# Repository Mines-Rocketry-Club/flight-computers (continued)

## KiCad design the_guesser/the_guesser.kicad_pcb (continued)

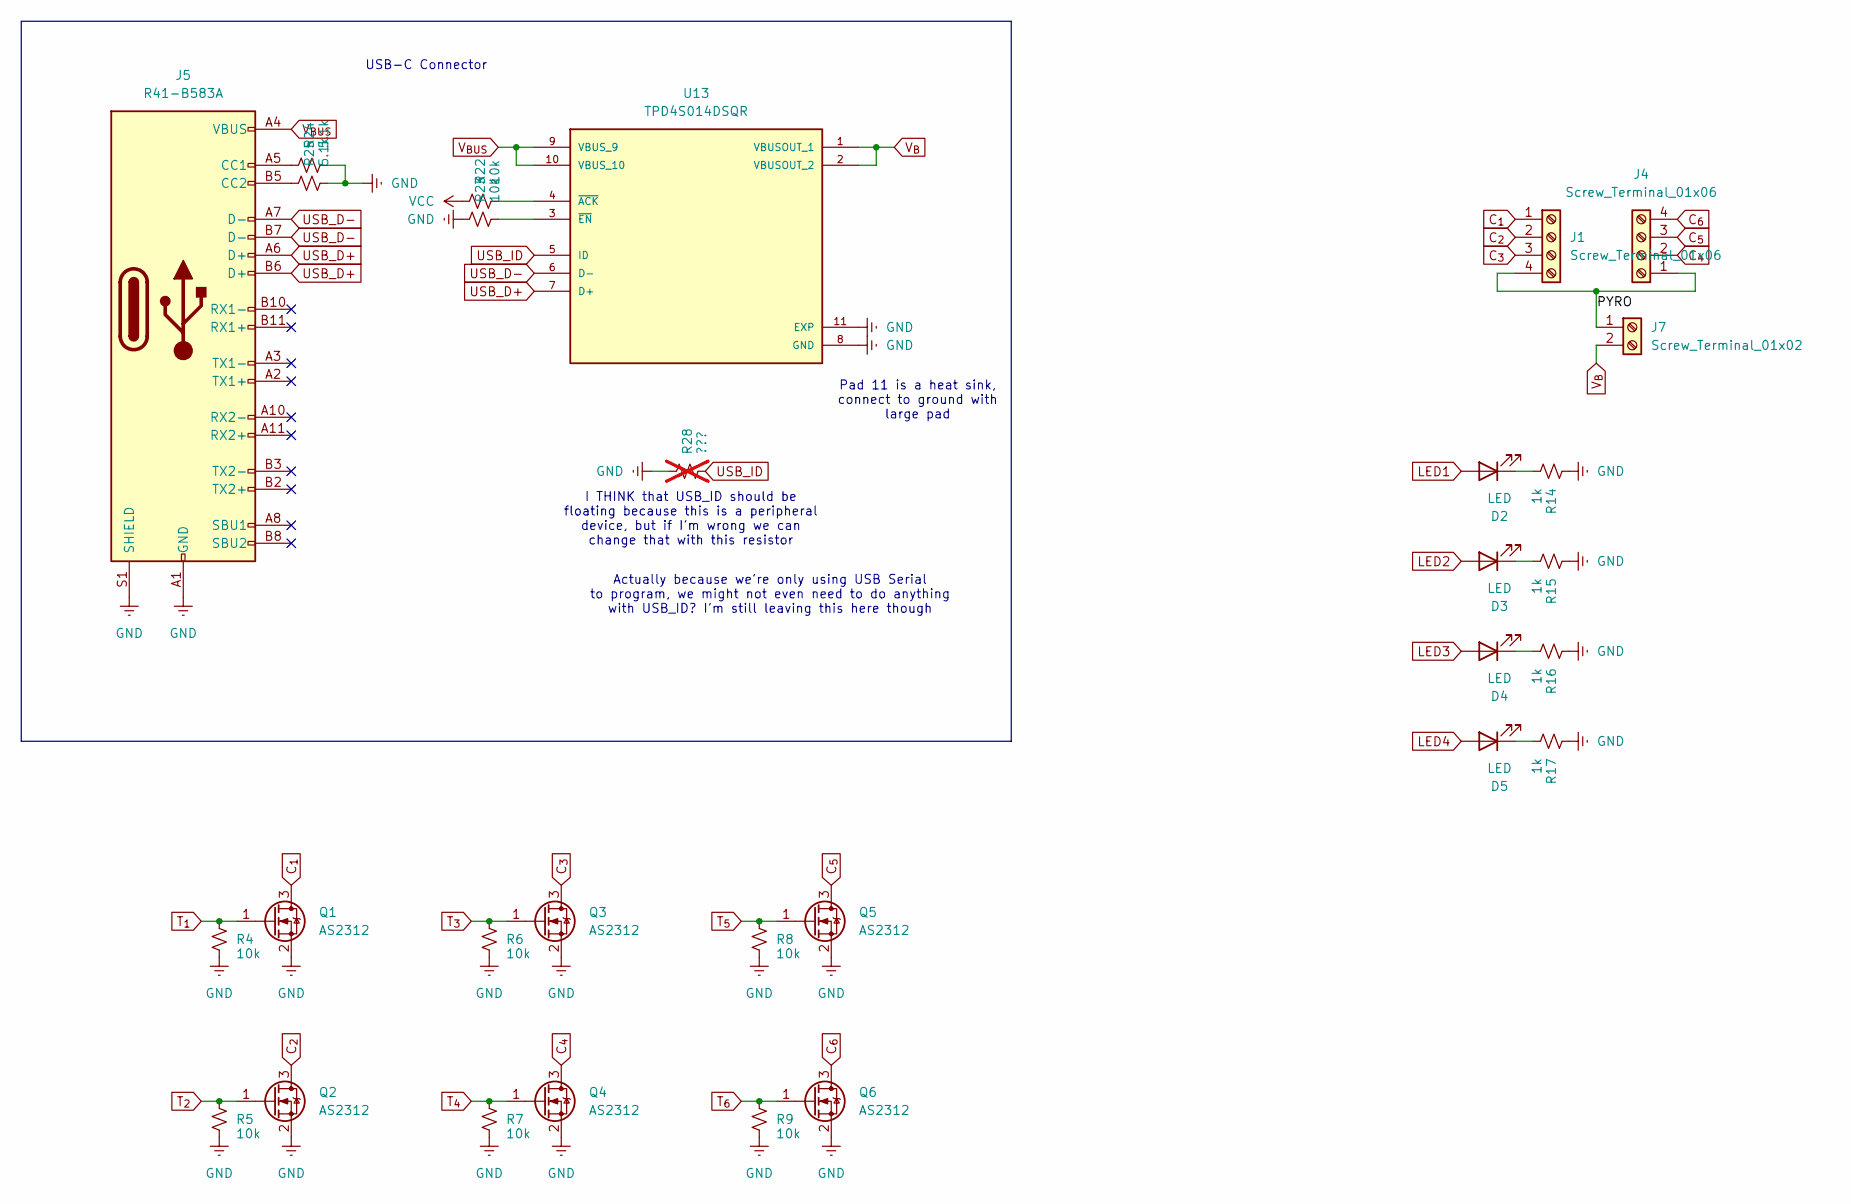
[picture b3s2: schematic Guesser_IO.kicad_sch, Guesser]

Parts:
D2, D3, D4, D5: LED; LED_0603_1608Metric
J1, J4: Screw_Terminal_01x06; TerminalBlock_Phoenix_MPT-0,5-4-2.54_1x04_P2.54mm_Horizontal
J5: R41-B583A; CONN_R41-B583A_MIT
J7: Screw_Terminal_01x02; TerminalBlock_Phoenix_MPT-0,5-2-2.54_1x02_P2.54mm_Horizontal
Q1, Q2, Q3, Q4, Q5, Q6: AS2312; SOT-23
R4, R5, R6, R7, R8, R9, R22, R23: 10k; R_0603_1608Metric
R14, R15, R16, R17: 1k; R_0603_1608Metric
R24, R25: 5.1k; R_0603_1608Metric
R28: ???; R_0603_1608Metric; not fitted
U13: TPD4S014DSQR; PARTREV E

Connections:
/Inputs Outputs/PYRO: J1.4, J4.1, J7.1
C_{1}: J1.1, Q1.3 (D)
C_{2}: J1.2, Q2.3 (D)
C_{3}: J1.3, Q3.3 (D)
C_{4}: J4.2, Q4.3 (D)
C_{5}: J4.3, Q5.3 (D)
C_{6}: J4.4, Q6.3 (D)
GND: J5.A1 (GND), J5.A12 (GND), J5.B1 (GND), J5.B12 (GND), J5.S1 (SHIELD), Q1.2 (S), Q2.2 (S), Q3.2 (S), Q4.2 (S), Q5.2 (S), Q6.2 (S), R4.2, R5.2, R6.2, R7.2, R8.2, R9.2, R14.1, R15.1, R16.1, R17.1, R23.1, R24.2, R25.2, R28.1, U13.8 (GND), U13.11 (EXP); also elsewhere on the board
LED1: D2.2 (A); also elsewhere on the board
LED2: D3.2 (A); also elsewhere on the board
LED3: D4.2 (A); also elsewhere on the board
LED4: D5.2 (A); also elsewhere on the board
unnamed: D2.1 (K), R14.2
unnamed: D3.1 (K), R15.2
unnamed: D4.1 (K), R16.2
unnamed: D5.1 (K), R17.2
unnamed: J5.A5 (CC1), R24.1
unnamed: J5.B5 (CC2), R25.1
unnamed: R22.2, U13.4 (~ACK)
unnamed: R23.2, U13.3 (~EN)
T_{1}: Q1.1 (G), R4.1; also elsewhere on the board
T_{2}: Q2.1 (G), R5.1; also elsewhere on the board
T_{3}: Q3.1 (G), R6.1; also elsewhere on the board
T_{4}: Q4.1 (G), R7.1; also elsewhere on the board
T_{5}: Q5.1 (G), R8.1; also elsewhere on the board
T_{6}: Q6.1 (G), R9.1; also elsewhere on the board
USB_D+: J5.A6 (D+), J5.B6 (D+), U13.7 (D+); also elsewhere on the board
USB_D-: J5.A7 (D-), J5.B7 (D-), U13.6 (D-); also elsewhere on the board
USB_ID: R28.2, U13.5 (ID)
VCC: R22.1; also elsewhere on the board
V_{BUS}: J5.A4 (VBUS), J5.A9 (VBUS), J5.B4 (VBUS), J5.B9 (VBUS), U13.9 (VBUS_9), U13.10 (VBUS_10)
V_{B}: J7.2, U13.1 (VBUSOUT_1), U13.2 (VBUSOUT_2); also elsewhere on the board

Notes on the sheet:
I THINK that USB_ID should be floating because this is a peripheral device, but if I'm wrong we can change that with this resistor
USB-C Connector
Actually because we're only using USB Serial to program, we might not even need to do anything with USB_ID? I'm still leaving this here though
Pad 11 is a heat sink, connect to ground with large pad

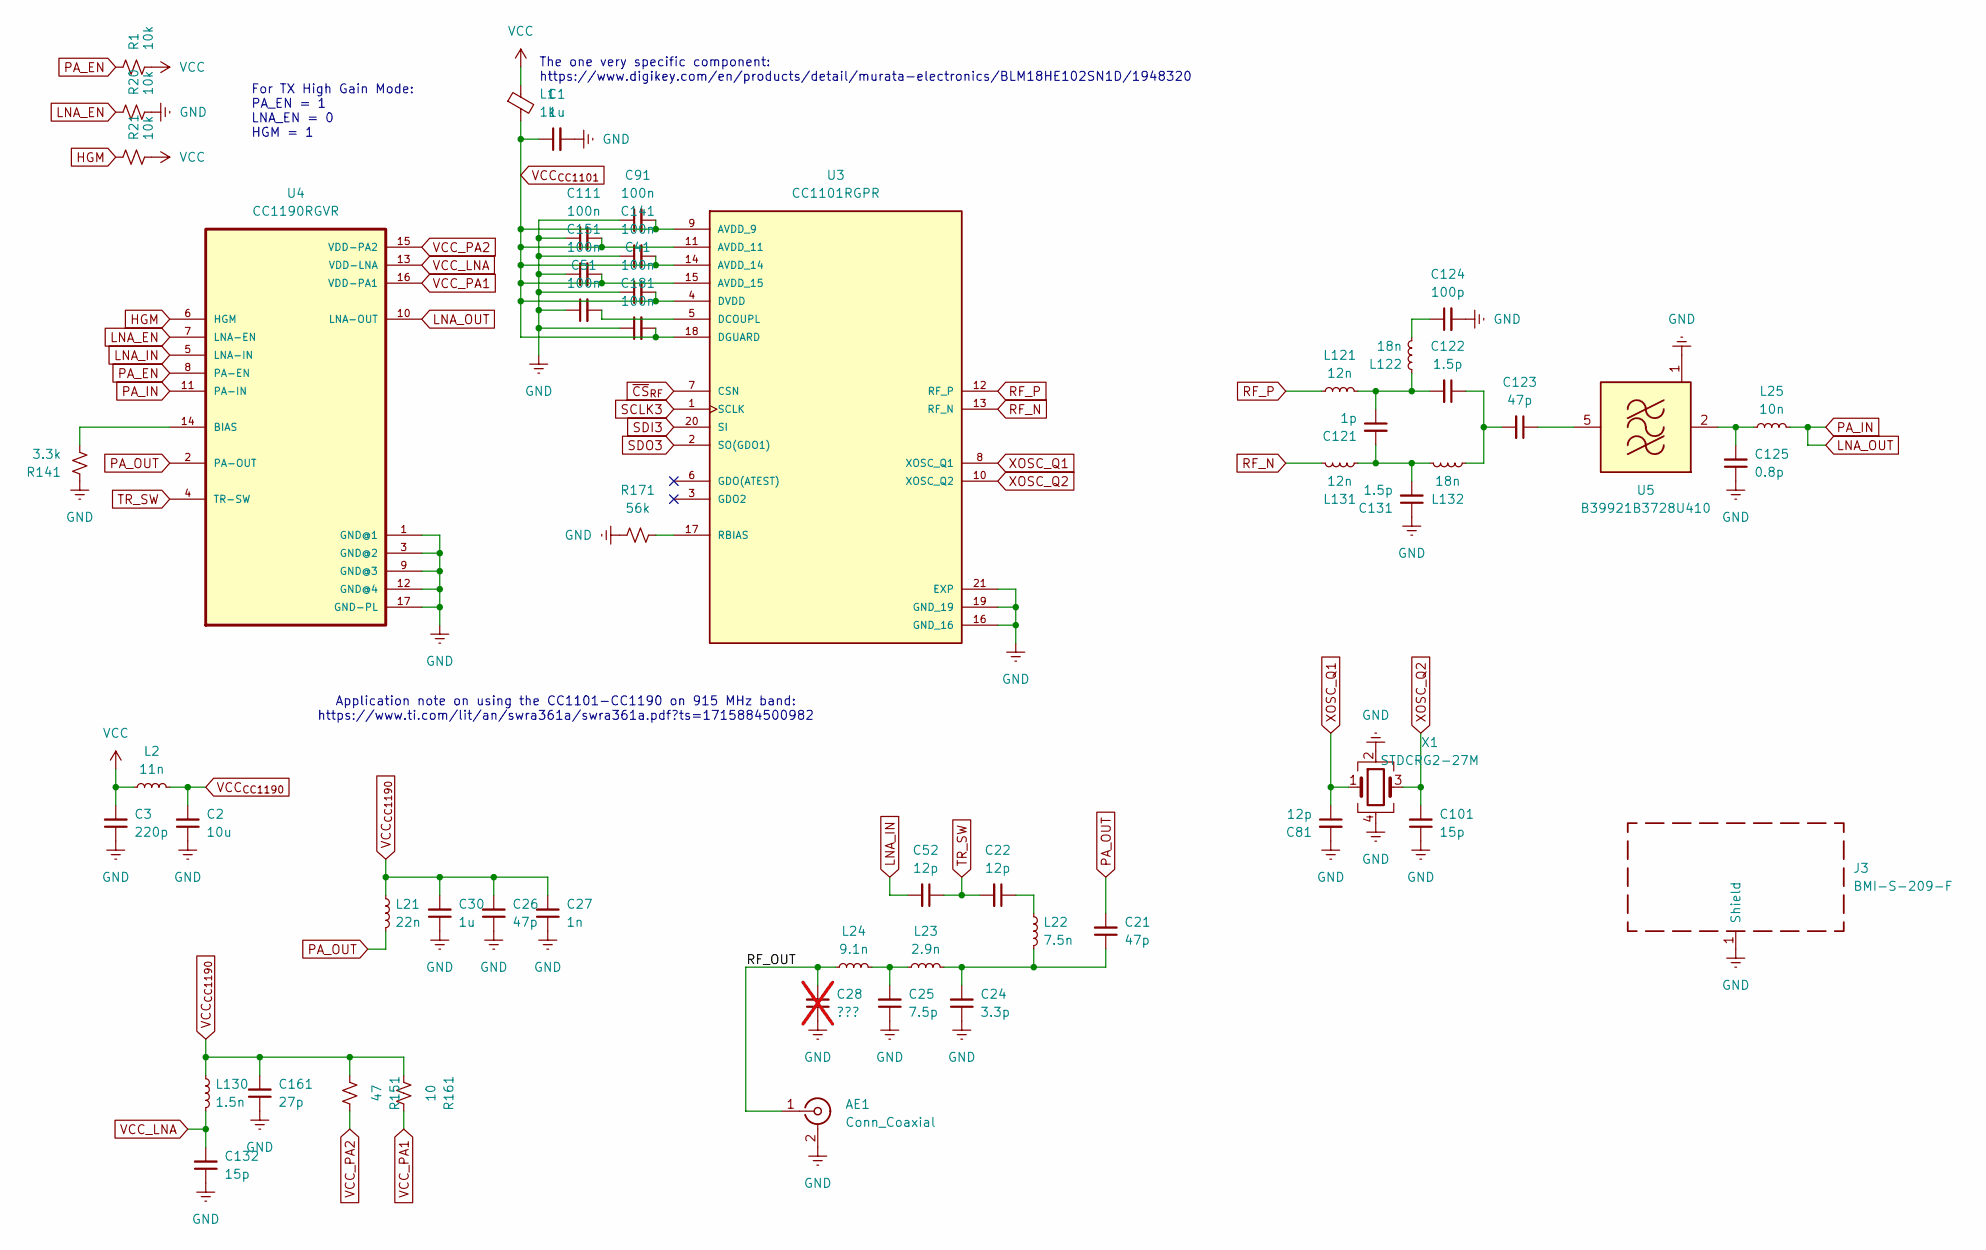
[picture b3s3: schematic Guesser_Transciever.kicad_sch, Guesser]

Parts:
AE1: Conn_Coaxial; SMA_Samtec_SMA-J-P-X-ST-EM1_EdgeMount
C1, C30: 1u; C_0603_1608Metric
C2: 10u; C_0603_1608Metric
C3: 220p; C_0603_1608Metric
C21, C26, C123: 47p; C_0603_1608Metric
C22, C52, C81: 12p; C_0603_1608Metric
C24: 3.3p; C_0603_1608Metric
C25: 7.5p; C_0603_1608Metric
C27: 1n; C_0603_1608Metric
C28: ???; C_0603_1608Metric; not fitted
C41, C51, C91, C111, C141, C151, C181: 100n; C_0603_1608Metric
C101, C132: 15p; C_0603_1608Metric
C121: 1p; C_0603_1608Metric
C122, C131: 1.5p; C_0603_1608Metric
C124: 100p; C_0603_1608Metric
C125: 0.8p; C_0603_1608Metric
C161: 27p; C_0603_1608Metric
J3: BMI-S-209-F; Laird_Technologies_BMI-S-209-F_29.36x18.50mm
L1: 1k; L_0603_1608Metric
L2: 11n; L_0603_1608Metric
L21: 22n; L_0603_1608Metric
L22: 7.5n; L_0603_1608Metric
L23: 2.9n; L_0603_1608Metric
L24: 9.1n; L_0603_1608Metric
L25: 10n; L_0603_1608Metric
L121, L131: 12n; L_0603_1608Metric
L122, L132: 18n; L_0603_1608Metric
L130: 1.5n; L_0603_1608Metric
R1, R20, R21: 10k; R_0603_1608Metric
R141: 3.3k; R_0603_1608Metric
R151: 47; R_0603_1608Metric
R161: 10; R_0603_1608Metric
R171: 56k; R_0603_1608Metric
U3: CC1101RGPR; PARTREV 6-May-2020
U4: CC1190RGVR
U5: B39921B3728U410; Filter_SAW-6_3.8x3.8mm
X1: STDCRG2-27M; Crystal_SMD_3225-4Pin_3.2x2.5mm

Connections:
/Transmitter/RF_OUT: AE1.1 (In), C28.2, L24.1
GND: AE1.2 (Ext), C1.2, C2.1, C3.1, C24.1, C25.1, C26.1, C27.1, C28.1, C30.1, C41.1, C51.1, C81.2, C91.1, C101.1, C111.1, C124.2, C125.1, C131.1, C132.1, C141.1, C151.1, C161.1, C181.1, J3.1 (Shield), R20.2, R141.1, R171.1, U3.16 (GND_16), U3.19 (GND_19), U3.21 (EXP), U4.1 (GND@1), U4.3 (GND@2), U4.9 (GND@3), U4.12 (GND@4), U4.17 (GND-PL), U5.1 (GND), U5.3 (GND), U5.4 (GND), U5.6 (GND), X1.2, X1.4; also elsewhere on the board
HGM: R21.1, U4.6 (HGM)
LNA_EN: R20.1, U4.7 (LNA-EN)
LNA_IN: C52.2, U4.5 (LNA-IN)
LNA_OUT: L25.2, U4.10 (LNA-OUT), U4.11 (PA-IN)
unnamed: C21.1, C24.2, L22.2, L23.2
unnamed: C22.1, L22.1
unnamed: C25.2, L23.1, L24.2
unnamed: C121.1, C122.2, L121.2, L122.1
unnamed: C121.2, C131.2, L131.1, L132.2
unnamed: C122.1, C123.2, L132.1
unnamed: C124.1, L122.2
unnamed: C51.2, U3.5 (DCOUPL)
unnamed: R171.2, U3.17 (RBIAS)
unnamed: R141.2, U4.14 (BIAS)
unnamed: C125.2, L25.1, U5.2 (IN)
unnamed: C123.1, U5.5 (OUT)
PA_EN: R1.1, U4.8 (PA-EN)
PA_OUT: C21.2, L21.2, U4.2 (PA-OUT)
RF_N: L131.2, U3.13 (RF_N)
RF_P: L121.1, U3.12 (RF_P)
SCLK3: U3.1 (SCLK); also elsewhere on the board
SDI3: U3.20 (SI); also elsewhere on the board
SDO3: U3.2 (SO(GDO1)); also elsewhere on the board
TR_SW: C22.2, C52.1, U4.4 (TR-SW)
VCC: C3.2, L1.1, L2.1, R1.2, R21.2; also elsewhere on the board
VCC_LNA: C132.2, L130.2, U4.13 (VDD-LNA)
VCC_PA1: R161.2, U4.16 (VDD-PA1)
VCC_PA2: R151.2, U4.15 (VDD-PA2)
VCC_{CC1101}: C1.1, C41.2, C91.2, C111.2, C141.2, C151.2, C181.2, L1.2, U3.4 (DVDD), U3.9 (AVDD_9), U3.11 (AVDD_11), U3.14 (AVDD_14), U3.15 (AVDD_15), U3.18 (DGUARD)
VCC_{CC1190}: C2.2, C26.2, C27.2, C30.2, C161.2, L2.2, L21.1, L130.1, R151.1, R161.1
XOSC_Q1: C81.1, U3.8 (XOSC_Q1), X1.1
XOSC_Q2: C101.2, U3.10 (XOSC_Q2), X1.3
~CS_{RF}: U3.7 (CSN); also elsewhere on the board

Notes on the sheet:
For TX High Gain Mode: PA_EN = 1 LNA_EN = 0 HGM = 1
Application note on using the CC1101-CC1190 on 915 MHz band: https://www.ti.com/lit/an/swra361a/swra361a.pdf?ts=1715884500982
The one very specific component: https://www.digikey.com/en/products/detail/murata-electronics/BLM18HE102SN1D/1948320

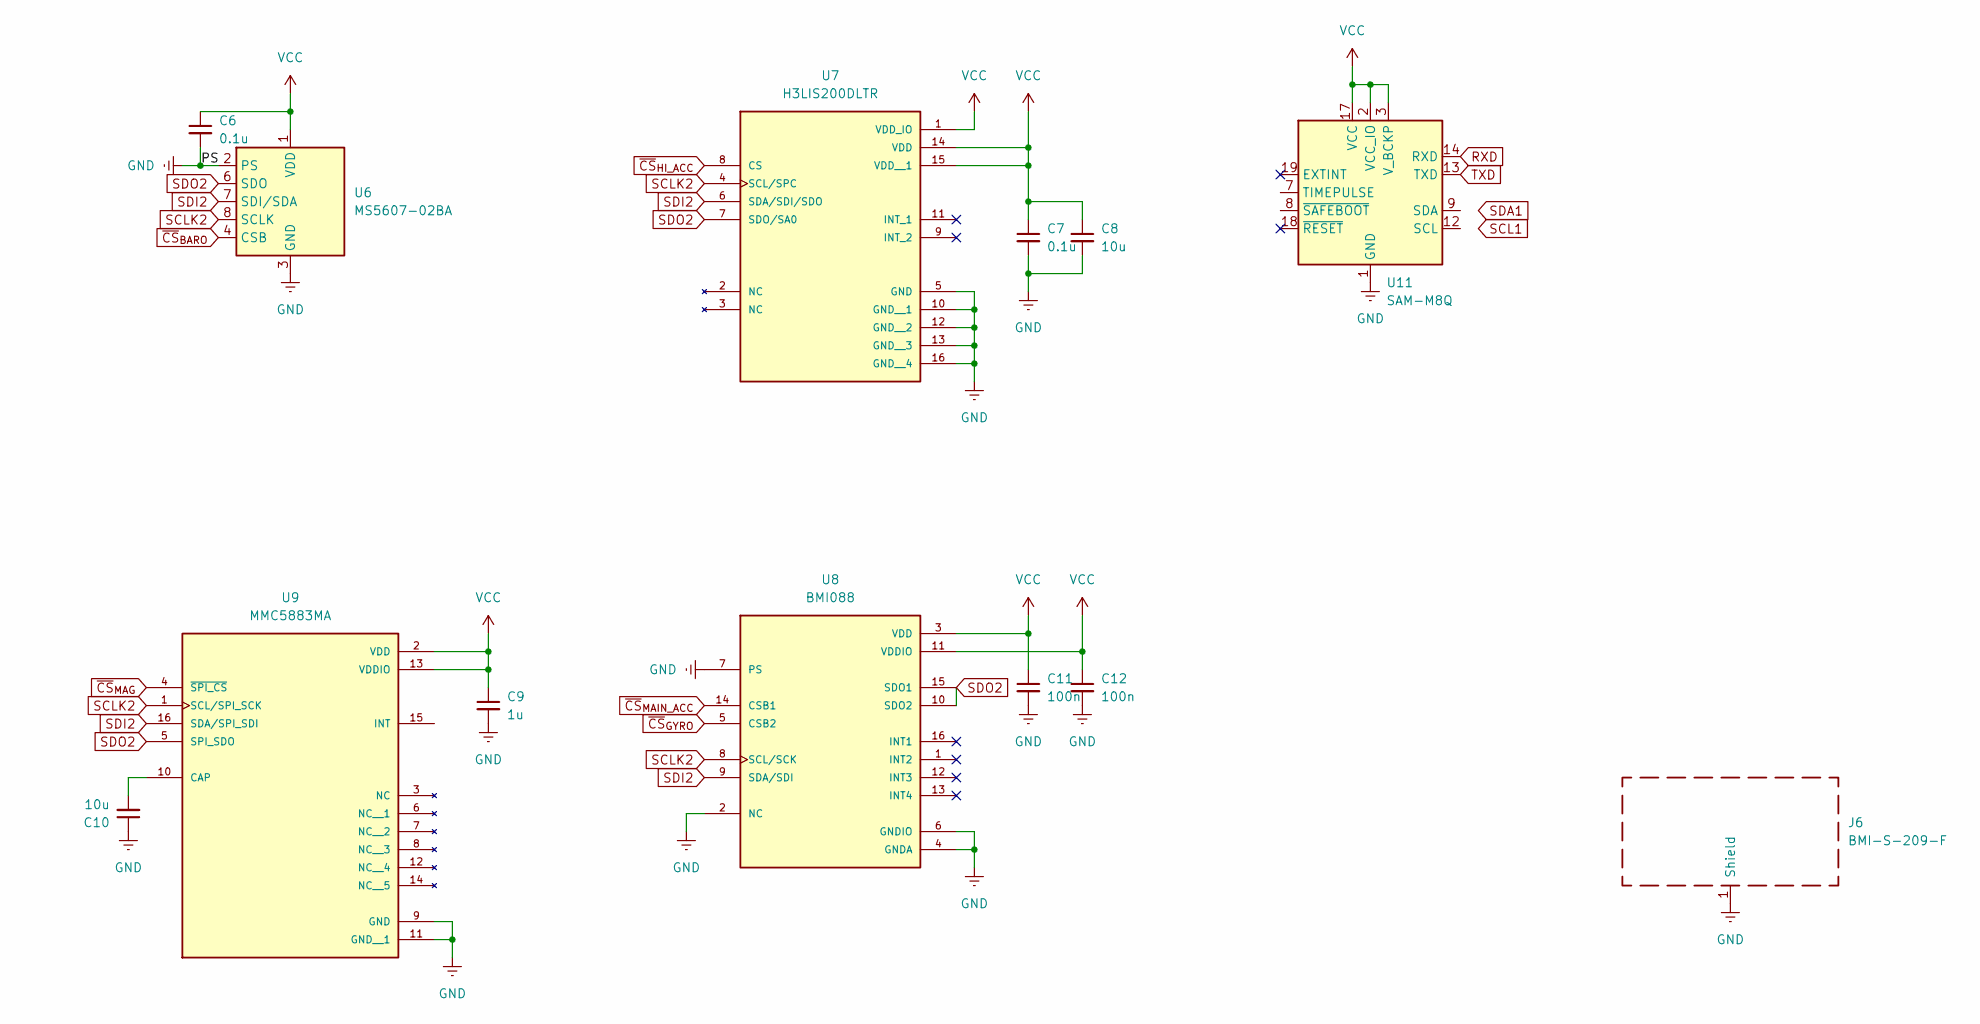
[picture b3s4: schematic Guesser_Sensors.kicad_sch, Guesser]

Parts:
C6, C7: 0.1u; C_0603_1608Metric
C8, C10: 10u; C_0603_1608Metric
C9: 1u; C_0603_1608Metric
C11, C12: 100n; C_0603_1608Metric
J6: BMI-S-209-F; Laird_Technologies_BMI-S-209-F_29.36x18.50mm
U6: MS5607-02BA; LGA-8_3x5mm_P1.25mm
U7: H3LIS200DLTR; PARTREV 2
U8: BMI088
U9: MMC5883MA; MMC5983MA; PARTREV A
U11: SAM-M8Q; ublox_SAM-M8Q

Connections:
GND: C6.2, C7.2, C8.2, C9.2, C10.1, C11.2, C12.2, J6.1 (Shield), U6.2 (PS), U6.3 (GND), U7.5 (GND), U7.10 (GND__1), U7.12 (GND__2), U7.13 (GND__3), U7.16 (GND__4), U8.2 (NC), U8.4 (GNDA), U8.6 (GNDIO), U8.7 (PS), U9.9 (GND), U9.11 (GND__1), U11.1 (GND), U11.4 (GND), U11.5 (GND), U11.6 (GND), U11.10 (GND), U11.11 (GND), U11.15 (GND), U11.16 (GND), U11.20 (GND); also elsewhere on the board
unnamed: C10.2, U9.10 (CAP)
RXD: U11.14 (RXD); also elsewhere on the board
SCLK2: U6.8 (SCLK), U7.4 (SCL/SPC), U8.8 (SCL/SCK), U9.1 (SCL/SPI_SCK); also elsewhere on the board
SDI2: U6.7 (SDI/SDA), U7.6 (SDA/SDI/SDO), U8.9 (SDA/SDI), U9.16 (SDA/SPI_SDI); also elsewhere on the board
SDO2: U6.6 (SDO), U7.7 (SDO/SA0), U8.10 (SDO2), U8.15 (SDO1), U9.5 (SPI_SDO); also elsewhere on the board
TXD: U11.13 (TXD); also elsewhere on the board
VCC: C6.1, C7.1, C8.1, C9.1, C11.1, C12.1, U6.1 (VDD), U7.1 (VDD_IO), U7.14 (VDD), U7.15 (VDD__1), U8.3 (VDD), U8.11 (VDDIO), U9.2 (VDD), U9.13 (VDDIO), U11.2 (VCC_IO), U11.3 (V_BCKP), U11.17 (VCC); also elsewhere on the board
~CS_{BARO}: U6.4 (CSB), U6.5 (CSB); also elsewhere on the board
~CS_{GYRO}: U8.5 (CSB2); also elsewhere on the board
~CS_{HI_ACC}: U7.8 (CS); also elsewhere on the board
~CS_{MAG}: U9.4 (~SPI_CS); also elsewhere on the board
~CS_{MAIN_ACC}: U8.14 (CSB1); also elsewhere on the board

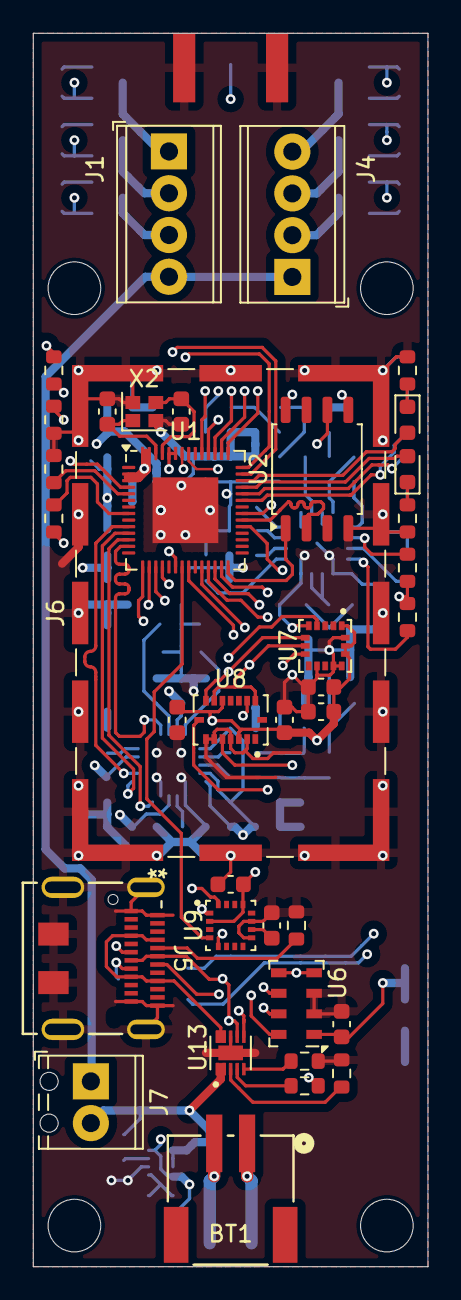
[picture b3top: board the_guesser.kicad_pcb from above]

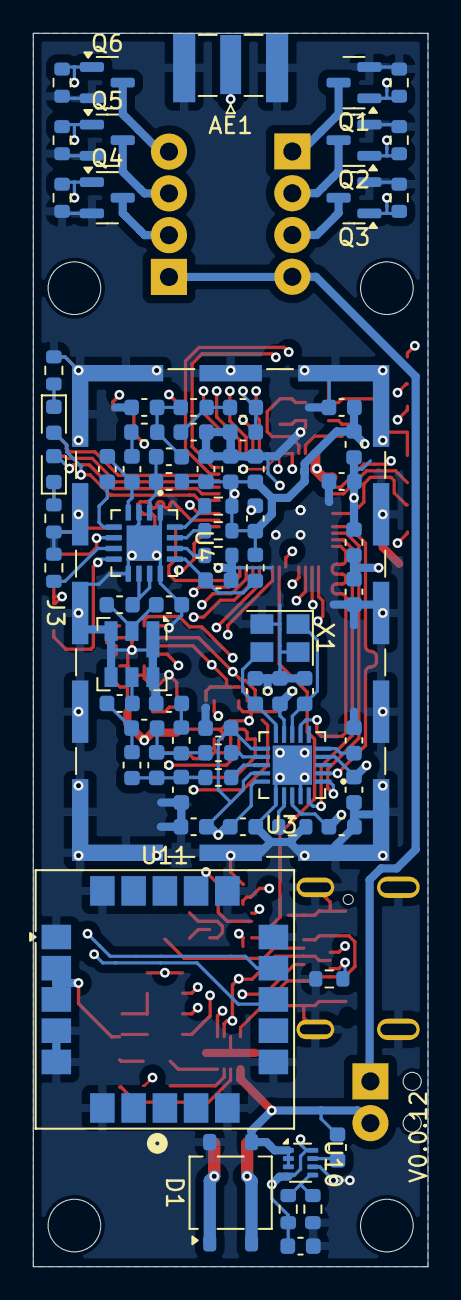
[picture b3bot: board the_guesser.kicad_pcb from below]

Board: 4 copper layers, 24.0 x 75.0 mm, 117 parts (76 on the bottom side), 90 nets.

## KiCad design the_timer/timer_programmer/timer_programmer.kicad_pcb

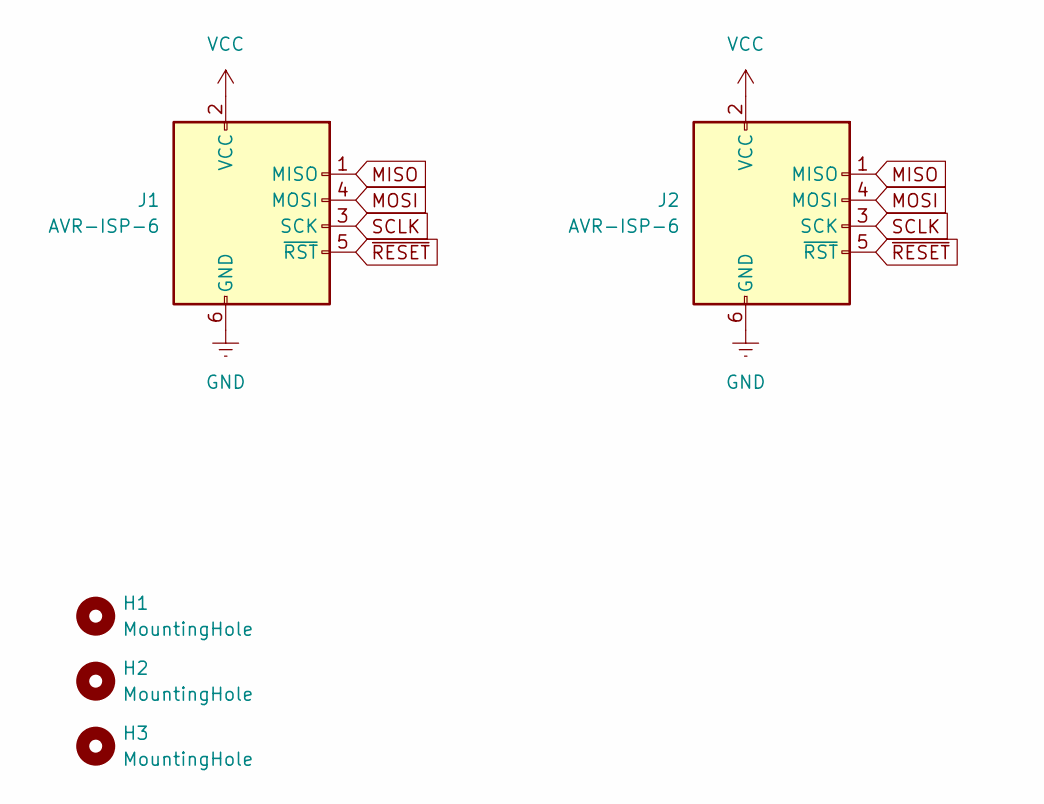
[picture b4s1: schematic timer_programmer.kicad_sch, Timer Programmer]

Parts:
H1, H2, H3: MountingHole; MountingHole_3.2mm_M3
J1: AVR-ISP-6; PinSocket_2x03_P1.27mm_Vertical
J2: AVR-ISP-6; PinHeader_2x03_P2.54mm_Horizontal

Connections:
GND: J1.6 (GND), J2.6 (GND)
MISO: J1.1 (MISO), J2.1 (MISO)
MOSI: J1.4 (MOSI), J2.4 (MOSI)
SCLK: J1.3 (SCK), J2.3 (SCK)
VCC: J1.2 (VCC), J2.2 (VCC)
~RESET: J1.5 (~RST), J2.5 (~RST)

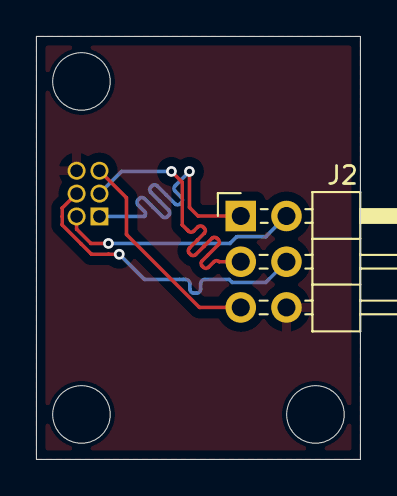
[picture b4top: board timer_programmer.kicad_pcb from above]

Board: 2 copper layers, 18.0 x 23.5 mm, 5 parts (1 on the bottom side), 6 nets.

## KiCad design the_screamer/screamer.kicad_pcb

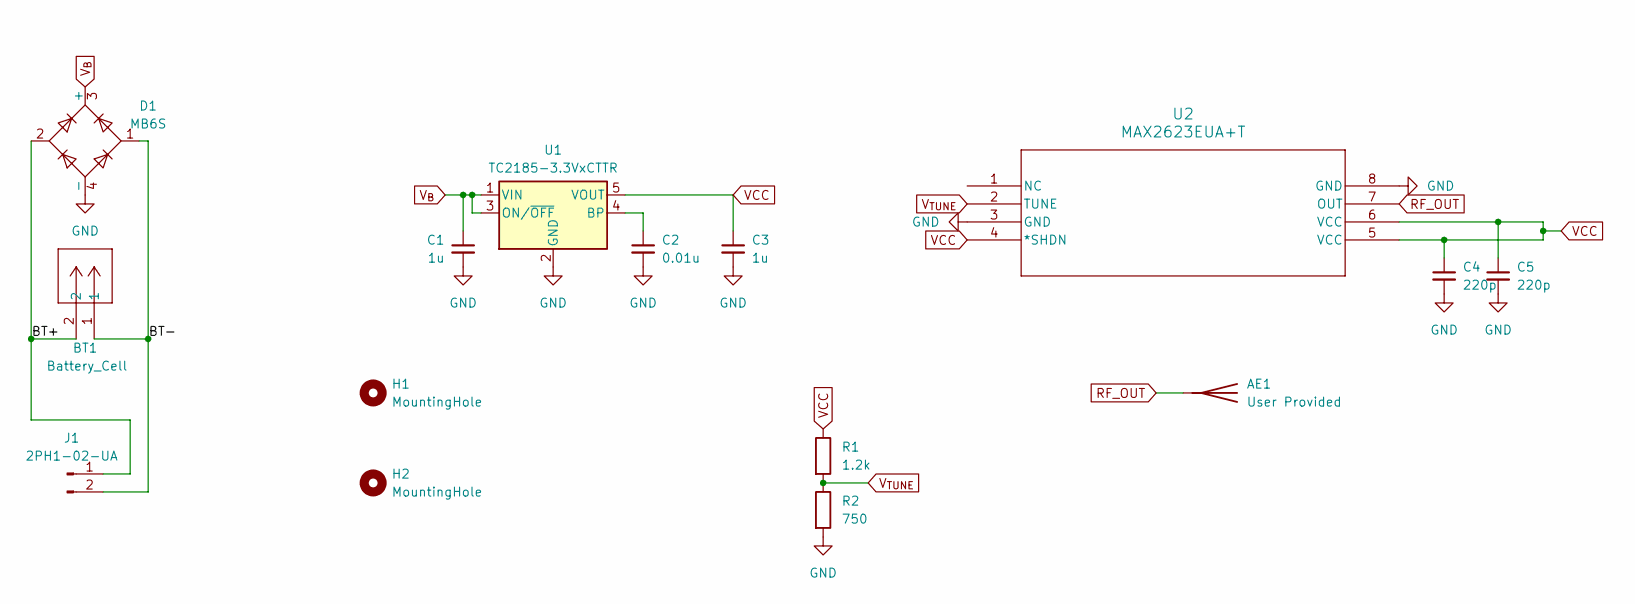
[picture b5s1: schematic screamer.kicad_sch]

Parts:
AE1: User Provided; SolderWire-0.5sqmm_1x01_D0.9mm_OD2.1mm
BT1: Battery_Cell; CONN2_1775469-2_TEC
C1, C3: 1u; C_0603_1608Metric
C2: 0.01u; C_0603_1608Metric
C4, C5: 220p; C_0603_1608Metric
D1: MB6S; TO-269AA
H1, H2: MountingHole; MountingHole_3.2mm_M3
J1: 2PH1-02-UA; PinHeader_1x02_P2.00mm_Vertical
R1: 1.2k; R_0603_1608Metric
R2: 750; R_0603_1608Metric
U1: TC2185-3.3VxCTTR; SOT-23-5
U2: MAX2623EUA+T; MSOP-8_3x3mm_P0.65mm

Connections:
/BT+: BT1.2, D1.2, J1.1
/BT-: BT1.1, D1.1, J1.2
GND: C1.2, C2.2, C3.2, C4.2, C5.2, D1.4 (-), R2.2, U1.2 (GND), U2.3 (GND), U2.8 (GND)
unnamed: C2.1, U1.4 (BP)
RF_OUT: AE1.1 (A), U2.7 (OUT)
VCC: C3.1, C4.1, C5.1, R1.1, U1.5 (VOUT), U2.4 (*SHDN), U2.5 (VCC), U2.6 (VCC)
V_{B}: C1.1, D1.3 (+), U1.1 (VIN), U1.3 (ON/~OFF)
V_{TUNE}: R1.2, R2.1, U2.2 (TUNE)

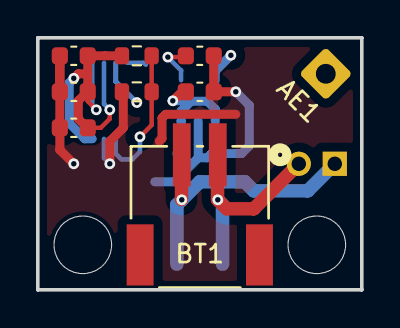
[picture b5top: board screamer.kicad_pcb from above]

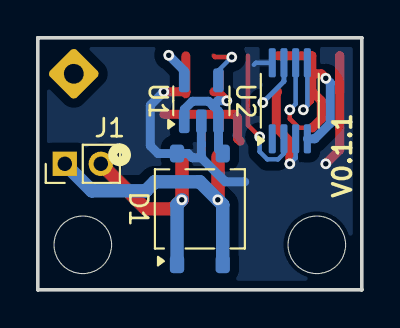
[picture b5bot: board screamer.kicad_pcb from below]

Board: 4 copper layers, 18.0 x 14.0 mm, 15 parts (4 on the bottom side), 8 nets.

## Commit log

2024-04-09 update gitignore
2024-04-09 init new projects, bring in the timers
2024-04-09 begin project resource library
2024-04-09 added memory to the timer
2024-04-09 added missing footprint library
2024-04-10 Finished rerouting timer
2024-04-10 began work on guesser schematics
2024-04-10 created project common symbols library & guesser work
2024-04-11 placed several chips
2024-04-11 work on the screamer and some R analysis code
2024-04-11 gitignore changed, i guess
2024-04-11 plotting gains
2024-04-11 commit to defuck the libraries
2024-04-12 Updates to Timer
    fuckkkkkkkkkkkkkkkkkkk
2024-04-12 screamer sch work
2024-04-12 cleanup and global sym lib
2024-04-12 final screamer schematics
2024-04-12 Create HW_LICENSE
    Moved all hardware implementations under the TAPR Open Hardware License (OHL)
2024-04-12 Rename LICENSE to FW_LICENSE
    Parity with README
2024-04-12 Timer is "done"
2024-04-12 i moved a trace .2mm
2024-04-13 added second battery terminal
2024-04-15 The squincher did the squinch
2024-04-15 Added connector to Screamer
2024-04-15 Cleaned up Screamer vias
    Also this is a reminder to NOT TOUCH the new "locals_but_working_PLEASE.pretty" folder that I created.
2024-04-16 De-squinched the Screamer
    Board is now 18x14 mm. I also moved the antenna position and cleaned up the silkscreen.
2024-04-16 Adjusted Screamer vias
2024-04-16 hell hell hell hell hell hell hell hell hell
    updated timer to have a better layout and header pins. This layout is NOT yet screamer compatible and is not final
2024-04-16 inner: resolve
2024-04-16 work on the screamer and some R analysis code inner inner fix merge
2024-04-16 potential fix for broken kicad files
2024-04-16 work
2024-04-19 Guesser now works with timer
    :3
2024-04-20 Added Timer power connector
2024-04-20 Make the github fucking work
2024-04-20 Added resistor values to the voltage divider
    The resistors are 681 ohms and 1.2k ohms. I also adjusted some stuff on the silkscreen to make it more readable.
2024-04-23 Started on Timer code
2024-04-23 Revert "Merge branch 'main' of https://github.com/CSM-Rocketry-Club/flight-computers"
    This reverts commit 3edd037536e7f8eb1c97200e83282850b3e66c85, reversing
    changes made to 45bb795bdd8a498dcdd2092ff2f1a03ff2b1d69a.
2024-04-23 Revert "Started on Timer code"
    This reverts commit 45bb795bdd8a498dcdd2092ff2f1a03ff2b1d69a.
2024-04-23 Started on the Timer code (for real)
    updated the gitignore!
2024-04-24 repair timer files from the merge
2024-04-24 begin work on the desktop programming app
2024-04-24 update gitignore for rust app
2024-04-24 More work on fleshing out timer code
2024-04-25 PyroCharge Class close to done
2024-04-27 Added altimeter class
2024-04-27 weekends'
2024-04-30 Further timer updates
2024-05-01 Created 3D models of V0.0.2 Screamer and Timer
2024-05-02 basic timer code done. needs I2C and flash storage still
2024-05-02 Revert "Merge branch 'main' of https://github.com/Mines-Rocketry-Club/flight-computers"
    This reverts commit 078ac57e77fd6677f6dff357334dcf35e5addb3e, reversing
    changes made to e052295e3eeb9c2af4a3152dedf6dc0942ce3b9b.
2024-05-02 Revert "basic timer code done. needs I2C and flash storage still"
    This reverts commit e052295e3eeb9c2af4a3152dedf6dc0942ce3b9b.
2024-05-02 Reapply "Merge branch 'main' of https://github.com/Mines-Rocketry-Club/flight-computers"
    This reverts commit 4217abac3257780637590a0b5727a620ce2e86cf.
2024-05-02 Reapply "basic timer code done. needs I2C and flash storage still"
    This reverts commit 842fa8577128e955ada3ada55c12d659330da4eb.
2024-05-02 Updated Screamer to V0.0.3
    Swapped VCO to MAX2623, adjusted filtering capacitors, and rerouted board.
2024-05-03 Adjusted Screamer RF OUT trace width
    Inductance is weird.
2024-05-07 Added decoupling cap to barometer and rotated IMU 45 deg
2024-05-08 Add Screamer passive component part numbers
2024-05-08 Updated barometer decoupling cap DKPN
2024-05-08 Standardized names on Timer schematic
2024-05-10 gathered data on pyro charges
2024-05-12 pyro charge analysis work
2024-05-13 Updated timer PCB
    this might just be the worst board ever made
2024-05-14 Progress on altimeter implementation
2024-05-14 Added datasheets to Timer schematic
2024-05-15 Adjusted Timer labels
2024-05-15 Replaced Timer mosfets
2024-05-16 Generated Screamer and Timer BOMs
    Both Screamer and Timer have been bumped to V0.1.
2024-05-16 Fixed custom symbol file paths
    In addition to fixing all the file paths I also updated some symbols on the Timer and Screamer, updated the board characteristic tables, added missing 3D models to some components, and did a bit of o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
2024-05-16 Deleted redundant custom symbols and footprints
2024-05-16 Added automatic revision label to PCBs
2024-05-17 Started on Guesser transmitter schematic
2024-05-17 Tweaked timer traces a bit
2024-05-17 Routed Guesser RF components
2024-05-17 Altimeter class is ready for debugging & testing
2024-05-17 Minor change to FlightComputer.cpp that didn't get pushed
2024-05-18 Started Guesser sensor selection
2024-05-19 Started Guesser I/O and continued sensor selection
2024-05-20 Finished Guesser sensor selection and started sensor routing
2024-05-22 Routed USB and SPI buses
2024-05-22 Routed Guesser pyro channels
2024-05-22 Finished routing Guesser
2024-05-22 Started Timer Programmer
2024-05-23 Finished routing Timer Programmer
2024-05-23 Adjusted some Guesser vias
2024-05-27 Redesigned Timer Programmer
2024-05-27 Cleaned up Guesser schematic a bit
2024-05-28 Created the Pointer
    The Pointer schematic is derived from the V0.0.10 Guesser.
2024-05-29 Routed Pointer RF transmitter
2024-05-29 Routed Pointer GPS
2024-05-30 Swapped Pointer to ESP32-C3FH4
2024-05-30 Continued routing Pointer
2024-05-30 Updated Guesser USB and GPS
2024-06-02 Accelerometer code nearing completion
2024-06-02 yelling about the code being bad
2024-06-03 More yelling about the code being bad
2024-06-03 Gutted everything but data collection
2024-06-28 No idea what changed
2024-07-18 first pass on schematics. revisions to follow with pcb.
2024-09-04 Updated The Pointer???
    I don't actually know why it thinks I made a change but after every single time I open KiCad GitHub thinks that it's changed even though I haven't actually changed it so I'm just doing this to make G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
2025-12-06 Started Timer ESP32 redesign
    This redesign replaces the Timer's ATTINY88 with an ESP32-C3 to make it more compatible with the other flight computers. It also adds a USB-C port for easier programming.
    The Timer revision was started by copying the Guesser and removing everything unnecessary, then yoinking the ESP32-C3 off of the Pointer schematic, so everything is currently kinda a huge mess and so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
    Also it's currently in the "the_timer_2" folder so the old timer stuff is still referenceable. This will be changed later once I have unexploded the schematic and started the PCB design.
2025-12-09 Mostly de-exploded the schematic
    Also like sorta fixed the PCB design but not really but sorta
